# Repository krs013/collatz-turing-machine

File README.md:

# collatz-turing-machine
LED bar gadget that runs a Turing machine of the Collatz Conjecture algorithm for random numbers

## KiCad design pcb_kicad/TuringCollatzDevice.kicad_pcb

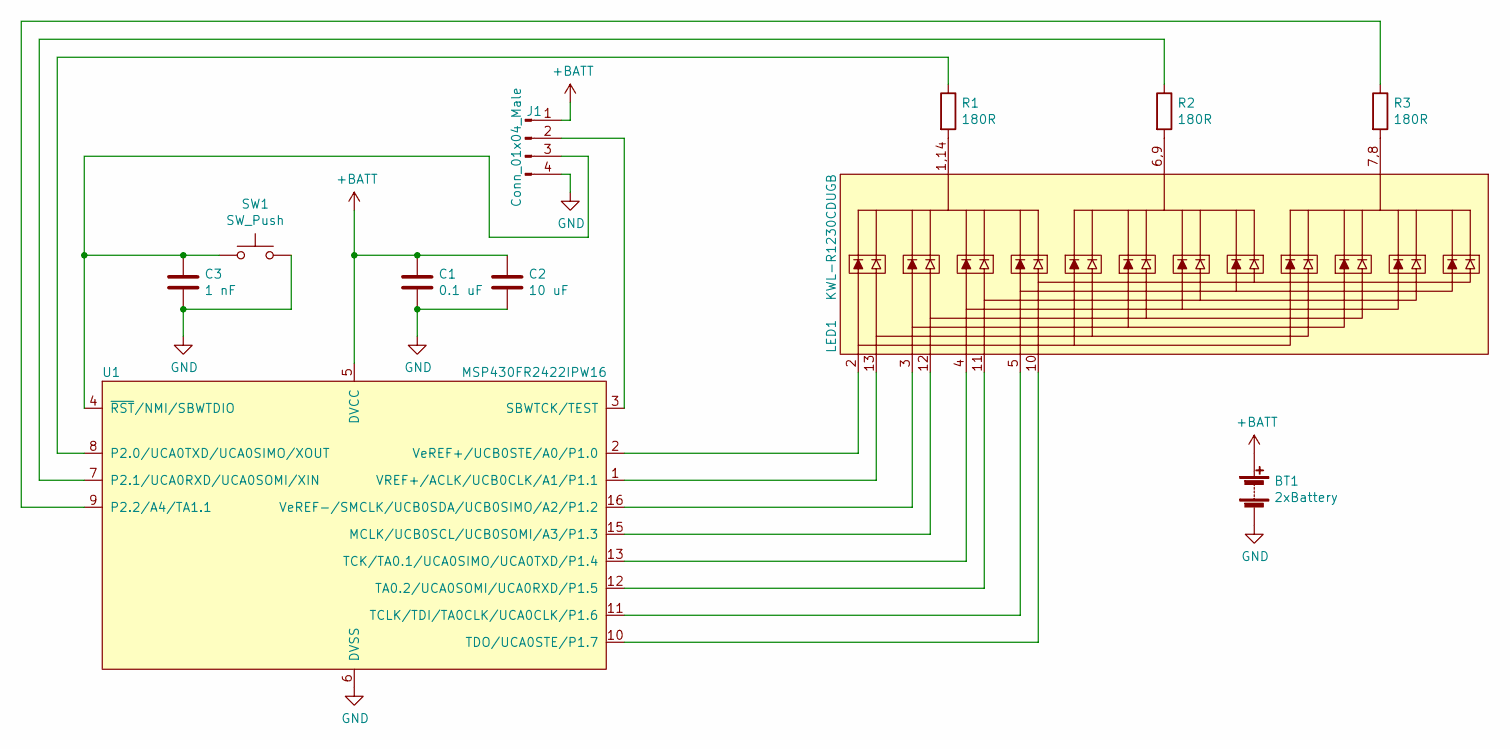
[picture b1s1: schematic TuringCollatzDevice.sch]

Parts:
BT1: 2xBattery; BatteryHolder_Keystone_2462_2xAA_NO_HOLES
C1: 0.1 uF; C_0603_1608Metric_Pad1.08x0.95mm_HandSolder
C2: 10 uF; C_0603_1608Metric_Pad1.08x0.95mm_HandSolder
C3: 1 nF; C_0603_1608Metric_Pad1.08x0.95mm_HandSolder
J1: Conn_01x04_Male; PinHeader_1x04_P2.54mm_Vertical
LED1: KWL-R1230CDUGB; DIP-14_Long_LED_Bar
R1, R2, R3: 180R; R_0603_1608Metric_Pad0.98x0.95mm_HandSolder
SW1: SW_Push; SW_PUSH_6mm
U1: MSP430FR2422IPW16; TSSOP-16_4.4x5mm_P0.65mm

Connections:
+BATT: BT1.1 (+), C1.1, C2.1, J1.1, U1.5 (DVCC)
GND: BT1.2 (-), C1.2, C2.2, C3.2, J1.4, SW1.2, U1.6 (DVSS)
unnamed: C3.1, J1.3, SW1.1, U1.4 (~RST~/NMI/SBWTDIO)
unnamed: J1.2, U1.3 (SBWTCK/TEST)
unnamed: LED1.1,14, R1.2
unnamed: LED1.2, U1.2 (VeREF+/UCB0STE/A0/P1.0)
unnamed: LED1.3, U1.16 (VeREF-/SMCLK/UCB0SDA/UCB0SIMO/A2/P1.2)
unnamed: LED1.4, U1.13 (TCK/TA0.1/UCA0SIMO/UCA0TXD/P1.4)
unnamed: LED1.5, U1.11 (TCLK/TDI/TA0CLK/UCA0CLK/P1.6)
unnamed: LED1.6,9, R2.2
unnamed: LED1.7,8, R3.2
unnamed: LED1.10, U1.10 (TDO/UCA0STE/P1.7)
unnamed: LED1.11, U1.12 (TA0.2/UCA0SOMI/UCA0RXD/P1.5)
unnamed: LED1.12, U1.15 (MCLK/UCB0SCL/UCB0SOMI/A3/P1.3)
unnamed: LED1.13, U1.1 (VREF+/ACLK/UCB0CLK/A1/P1.1)
unnamed: R1.1, U1.8 (P2.0/UCA0TXD/UCA0SIMO/XOUT)
unnamed: R2.1, U1.7 (P2.1/UCA0RXD/UCA0SOMI/XIN)
unnamed: R3.1, U1.9 (P2.2/A4/TA1.1)

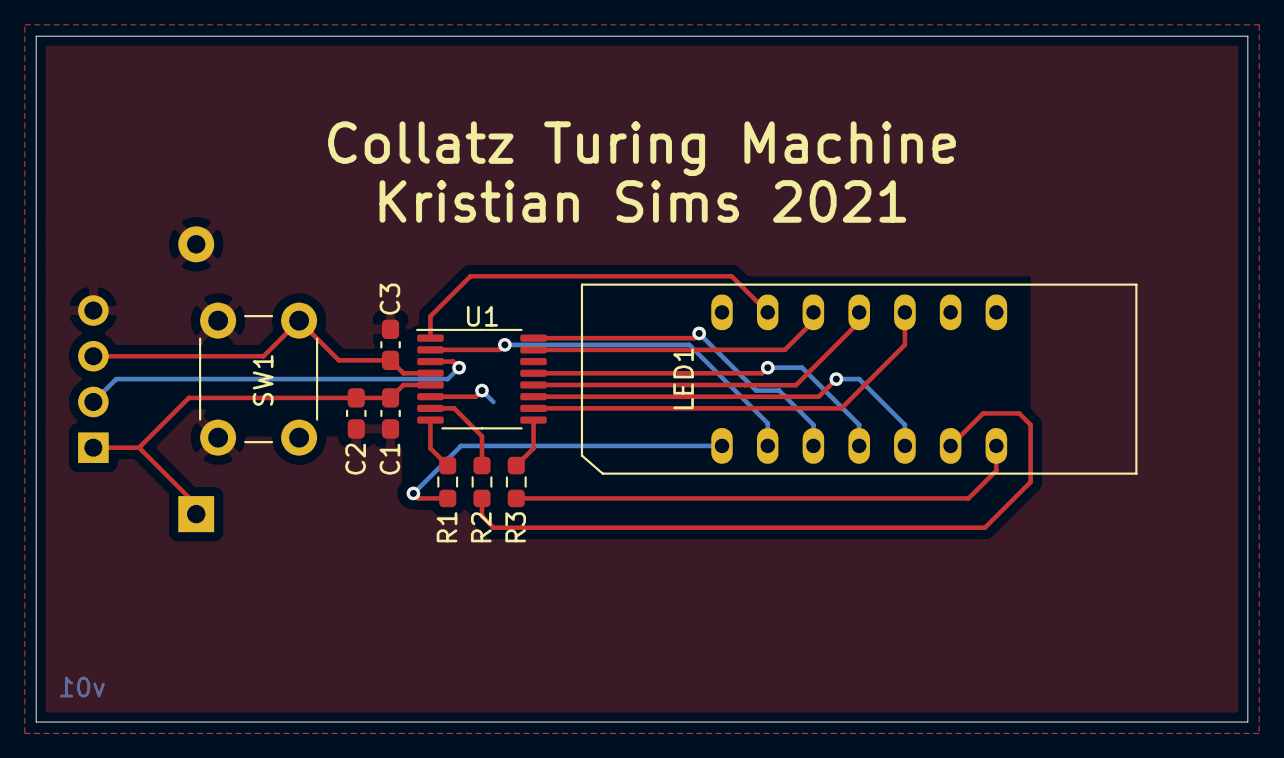
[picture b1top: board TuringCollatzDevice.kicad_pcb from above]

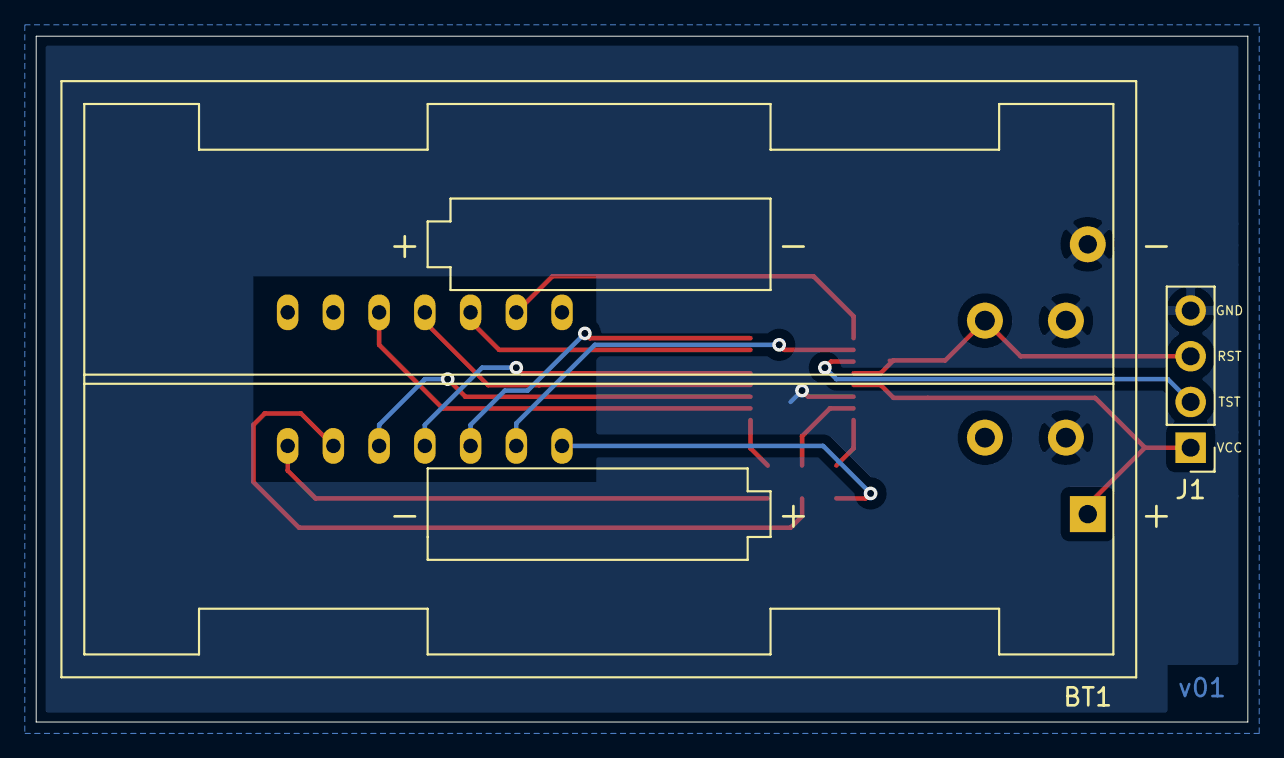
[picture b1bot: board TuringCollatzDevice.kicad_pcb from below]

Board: 2 copper layers, 67.3 x 38.1 mm, 11 parts (2 on the bottom side), 18 nets.

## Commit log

2021-07-14 First commit, working example on MSP4302422
2021-07-14 Add PCB files
2021-07-16 Improved tape animation, hacky and ugly but it works
2021-07-16 Added shutdown to save battery
2021-07-16 Disabled interrupts during update. It's less glitchy but more flickery. A double buffer would be better
2021-07-16 Added random starting numbers and LPM4.5. Done for now

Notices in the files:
pcb_kicad/TuringCollatzDevice.kicad_pcb:
License: CC BY 4.0
